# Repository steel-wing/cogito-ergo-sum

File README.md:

# clacken

*A short description of the keyboard/project*

* Keyboard Maintainer: [Carter Pollan](https://github.com/Carter Pollan)
* Hardware Supported: *The PCBs, controllers supported*
* Hardware Availability: *Links to where you can find this hardware*

Make example for this keyboard (after setting up your build environment):

    make clacken:default

Flashing example for this keyboard:

    make clacken:default:flash

See the [build environment setup](https://docs.qmk.fm/#/getting_started_build_tools) and the [make instructions](https://docs.qmk.fm/#/getting_started_make_guide) for more information. Brand new to QMK? Start with our [Complete Newbs Guide](https://docs.qmk.fm/#/newbs).

## Bootloader

Enter the bootloader in 3 ways:

* **Bootmagic reset**: Hold down the key at (0,0) in the matrix (usually the top left key or Escape) and plug in the keyboard
* **Physical reset button**: Briefly press the button on the back of the PCB - some may have pads you must short instead
* **Keycode in layout**: Press the key mapped to `QK_BOOT` if it is available

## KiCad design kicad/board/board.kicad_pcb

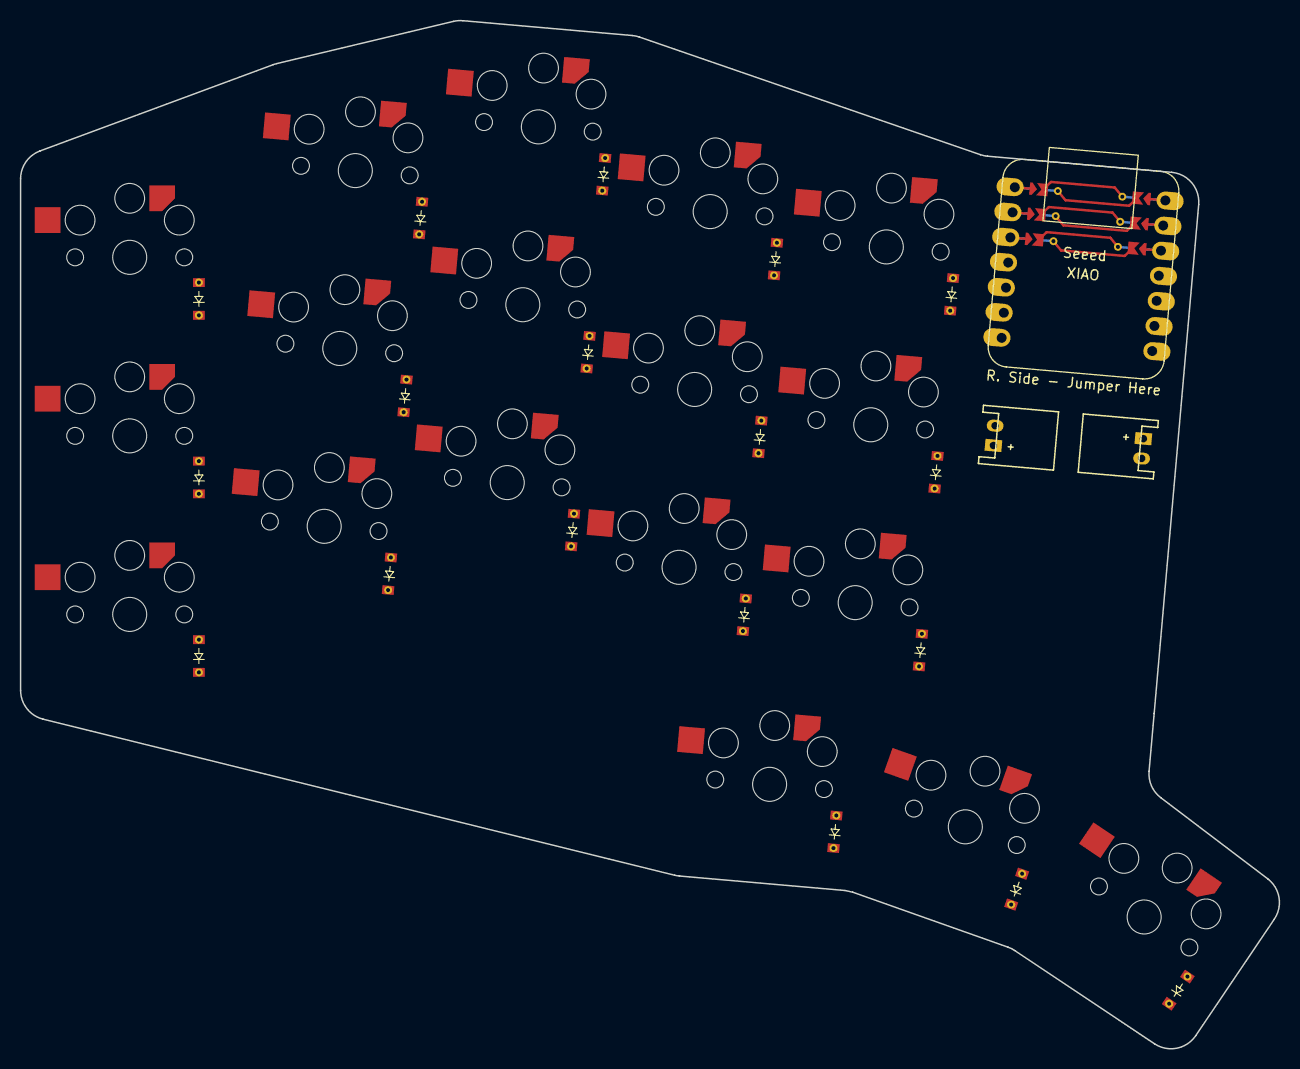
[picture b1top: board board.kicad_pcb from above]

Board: 2 copper layers, 126.9 x 103.7 mm, 39 parts (0 on the bottom side), 29 nets.

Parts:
D1, D2, D3, D4, D5, D6, D7, D8, D9, D10, D11, D12, D13, D14, D15, D16, D17, D18: 1N914; reversable_diode
JST1, JST2: Conn_01x02; JST_angled
S1, S2, S3, S4, S5, S6, S7, S8, S9, S10, S11, S12, S13, S14, S15, S16, S17, S18: SW_Push_45deg; choc_switches
U1: xiao-ble-tht

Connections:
Col1: S1.1, S2.1, S3.1
Col2: S4.1, S5.1, S6.1
Col3: S7.1, S8.1, S9.1, S16.1
Col4: S10.1, S11.1, S12.1, S17.1
Col5: S13.1, S14.1, S15.1, S18.1
unnamed: D1.2 (A), S1.2
unnamed: D2.2 (A), S2.2
unnamed: D3.2 (A), S3.2
unnamed: D4.2 (A), S4.2
unnamed: D5.2 (A), S5.2
unnamed: D6.2 (A), S6.2
unnamed: D7.2 (A), S7.2
unnamed: D8.2 (A), S8.2
unnamed: D9.2 (A), S9.2
unnamed: D10.2 (A), S10.2
unnamed: D11.2 (A), S11.2
unnamed: D12.2 (A), S12.2
unnamed: D13.2 (A), S13.2
unnamed: D14.2 (A), S14.2
unnamed: D15.2 (A), S15.2
unnamed: D16.2 (A), S16.2
unnamed: D17.2 (A), S17.2
unnamed: D18.2 (A), S18.2
unnamed: JST1.1, JST2.1
unnamed: JST1.2, JST2.2
Row1: D3.1 (K), D6.1 (K), D9.1 (K), D12.1 (K), D15.1 (K)
Row2: D2.1 (K), D5.1 (K), D8.1 (K), D11.1 (K), D14.1 (K)
Row3: D1.1 (K), D4.1 (K), D7.1 (K), D10.1 (K), D13.1 (K)
Row4: D16.1 (K), D17.1 (K), D18.1 (K)

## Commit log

2024-01-18 init of broken code
2024-01-21 changed so that all the keys except for the bottom right row works
2024-10-08 moved all of the qmk files into qmk folder
2024-10-08 init of ergogen files
2024-10-08 init of .gitignore
2024-10-08 init of README.md
2024-10-08 refactored ergogen files. Removed files that were unnessisary and moved others for simplicity
2024-10-08 init of board
2024-10-08 added relevent kicad files to gitignore
2024-10-10 init of footprints
2024-10-10 updated pcb
2024-10-10 updated xaio and made choc work again
2024-10-10 Fixed README nonsense
2024-10-17 github connections
